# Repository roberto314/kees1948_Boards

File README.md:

# kees1948_Boards
kees 1948 Uniflex Remake

This Repository is for my Remake of the PCBs from kees1948 FLEX and UniFLEX Project.
I like SMD Components and started with a new Version of the CPU09RAM Board with Battery Backup. 

I also started some modifications to the CPUXXCMI Board to run the Exorciser Firmware (Exbug) and in the near future i will make a Exordisk Hardware to read real floppies. See the Exorciser Subdirectory.

This is my Uniflex System:

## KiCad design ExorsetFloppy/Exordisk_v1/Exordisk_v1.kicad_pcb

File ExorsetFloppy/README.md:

# Motorola Exordisk Remake
for kees 1948 Board

This is a Remake of the Motorola Exordisk Board for kees1948 FLEX and UniFLEX Project.
Use it with a CPUXXCMI Board with a 6802 CPU @ 1MHz and the modifications on the Exorciser page.

Exordisk_v1 is the second revision of the Exordisk Board. Use this to build.

Exorset Floppy is the first version of the Exordisk board. It has a lot of problems!

In the GAL subdir. are the equations and .jed files for the exordisk remake board.

This is the Board:

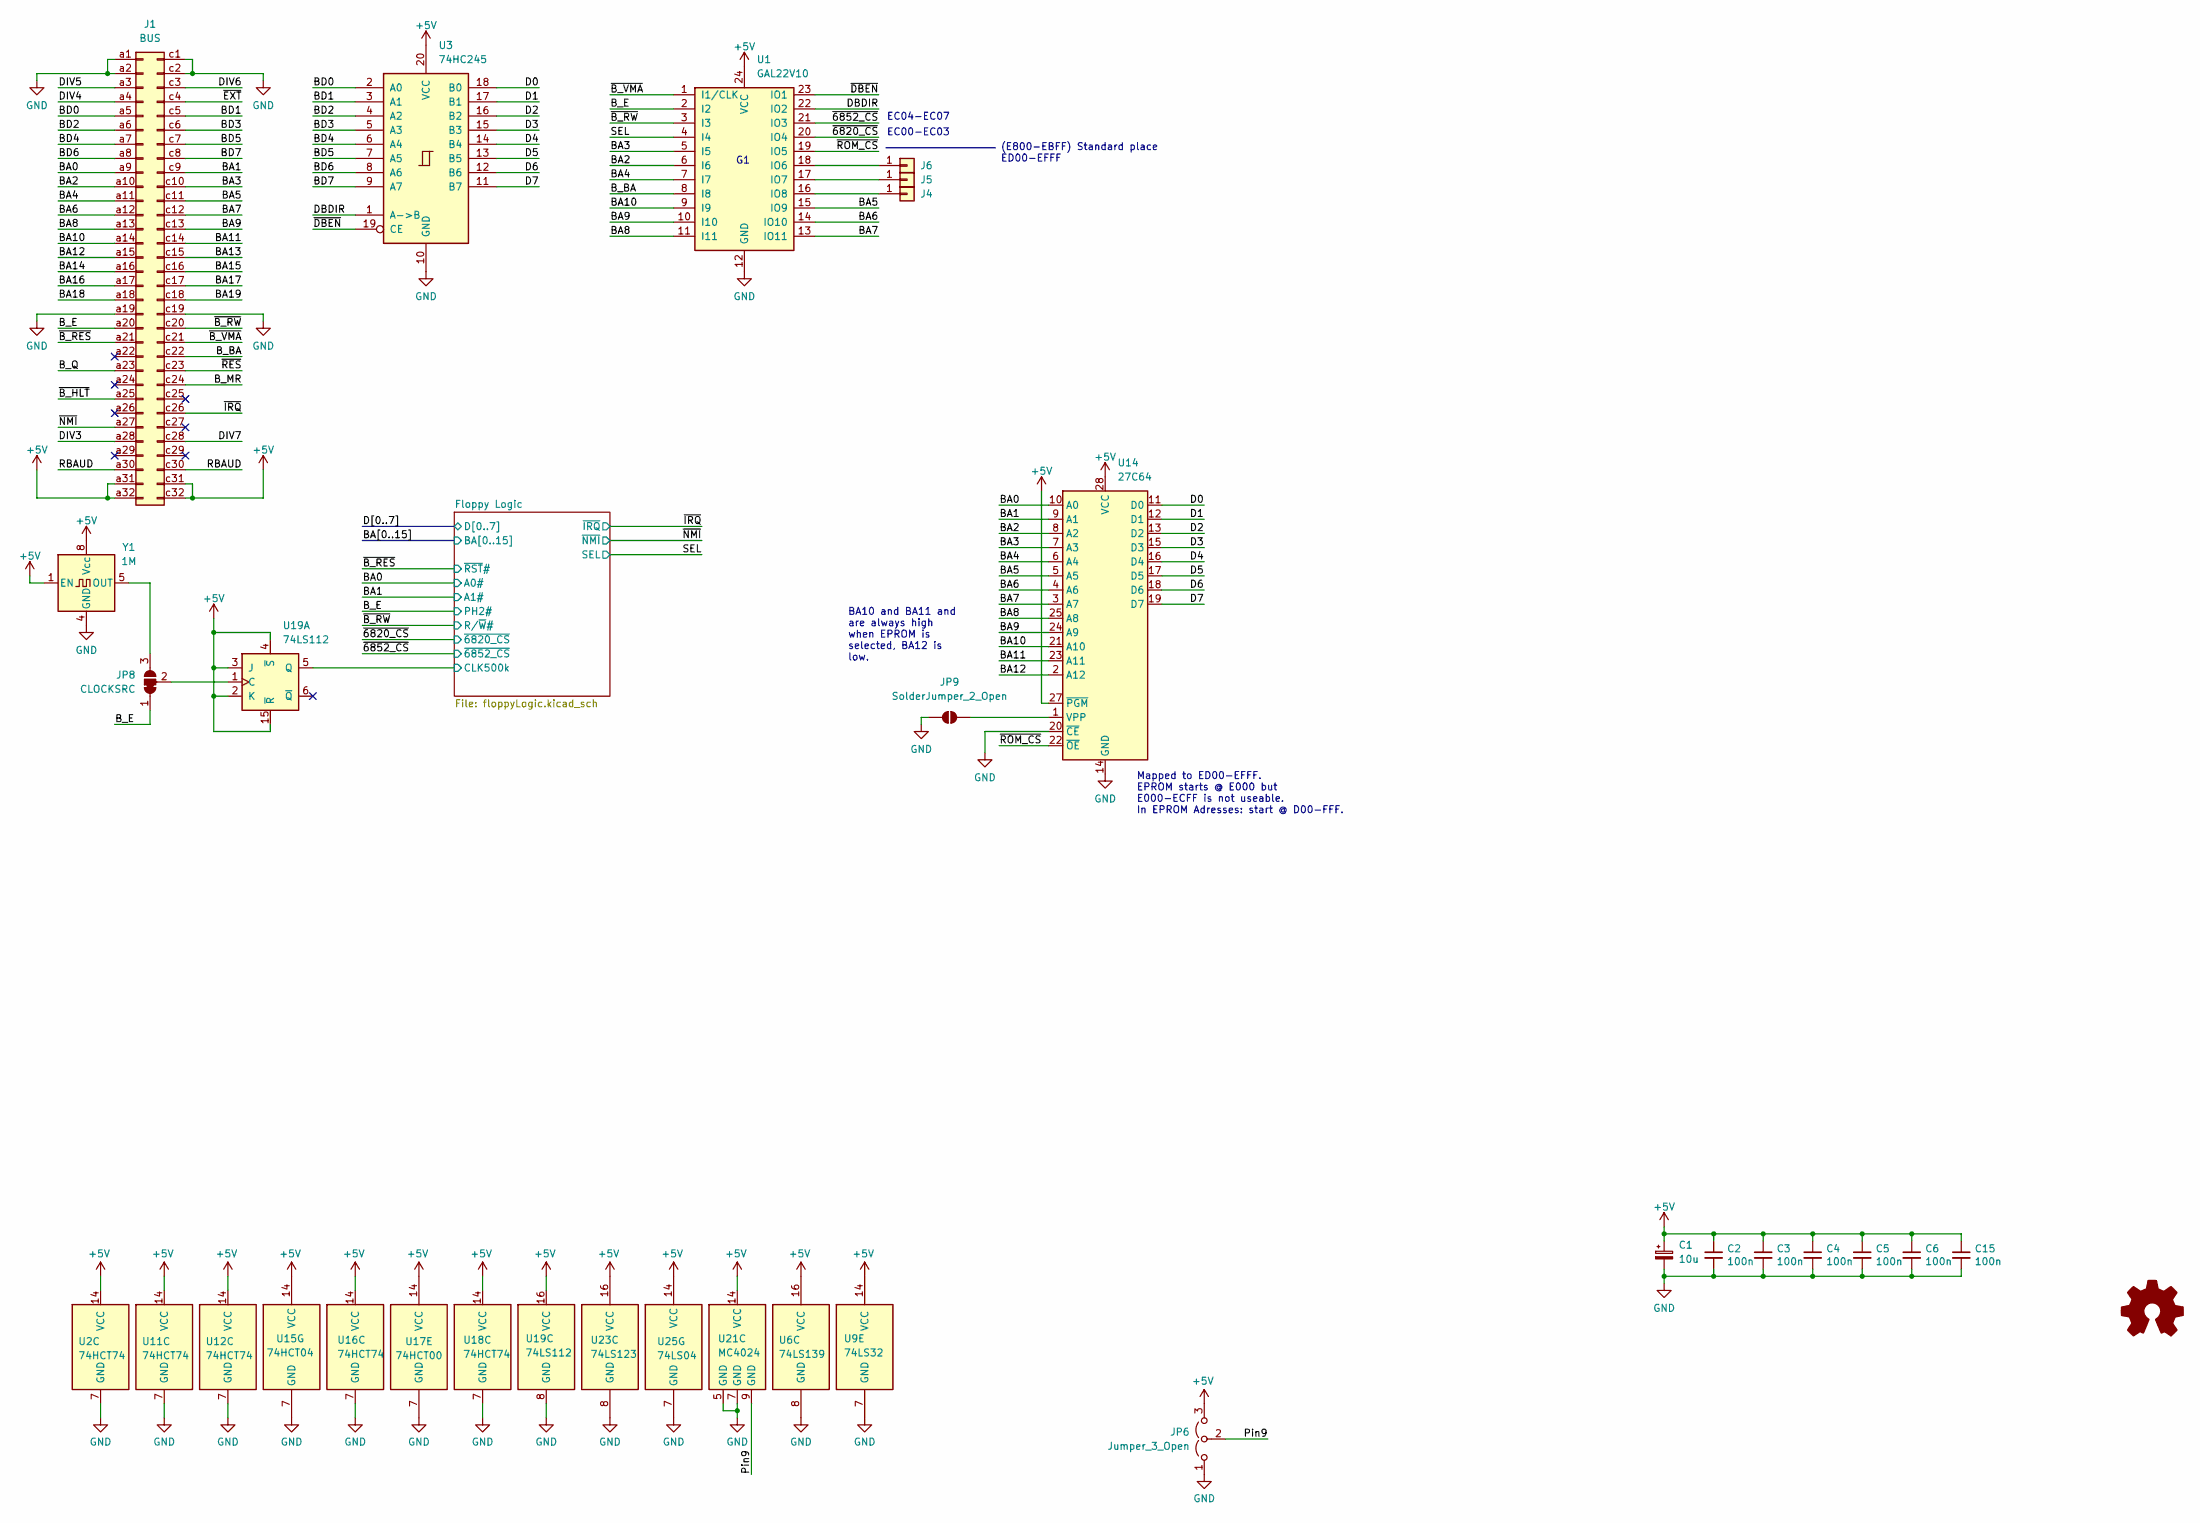
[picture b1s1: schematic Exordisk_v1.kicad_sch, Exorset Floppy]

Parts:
C1: 10u; CP_EIA-7343-31_Kemet-D_HandSolder
C2, C3, C4, C5, C6, C15: 100n; C_1206_3216Metric_Pad1.33x1.80mm_HandSolder
J1: BUS; DIN41612_C_2x32_Male_Horizontal_THT
J4, J5, J6: Conn_01x01; PinHeader_1x01_P2.54mm_Vertical
JP6: Jumper_3_Open; SolderJumper-3_P1.3mm_Open_RoundedPad1.0x1.5mm_NumberLabels
JP8: CLOCKSRC; SolderJumper-3_P1.3mm_Bridged12_RoundedPad1.0x1.5mm_NumberL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
JP9: SolderJumper_2_Open; SolderJumper-2_P1.3mm_Open_Pad1.0x1.5mm
U1: GAL22V10; DIP-24_W7.62mm
U2, U11, U12, U16, U18: 74HCT74; DIP-14_W7.62mm
U3: 74HC245; DIP-20_W7.62mm
U6: 74LS139; DIP-16_W7.62mm
U9: 74LS32; DIP-14_W7.62mm
U14: 27C64; DIP-28_W15.24mm
U15: 74HCT04; DIP-14_W7.62mm
U17: 74HCT00; DIP-14_W7.62mm
U19: 74LS112; DIP-16_W7.62mm
U21: MC4024; DIP-14_W7.62mm
U23: 74LS123; DIP-16_W7.62mm
U25: 74LS04; DIP-14_W7.62mm
Y1: 1M; Oscillator_DIP-8

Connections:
+5V: C1.1, C2.1, C3.1, C4.1, C5.1, C6.1, C15.1, J1.a31, J1.a32, J1.c31, J1.c32, JP6.3 (B), U1.24 (VCC), U2.14 (VCC), U3.20 (VCC), U6.16 (VCC), U9.14 (VCC), U11.14 (VCC), U12.14 (VCC), U14.27 (~PGM), U14.28 (VCC), U15.14 (VCC), U16.14 (VCC), U17.14 (VCC), U18.14 (VCC), U19.2 (K), U19.3 (J), U19.4 (~S), U19.15 (~R), U19.16 (VCC), U21.14 (VCC), U23.16 (VCC), U25.14 (VCC), Y1.1 (EN), Y1.8 (Vcc); also elsewhere on the board
/BA0: J1.a9, U14.10 (A0); also elsewhere on the board
/BA1: J1.c9, U14.9 (A1); also elsewhere on the board
/BA2: J1.a10, U1.6 (I6), U14.8 (A2)
/BA3: J1.c10, U1.5 (I5), U14.7 (A3)
/BA4: J1.a11, U1.7 (I7), U14.6 (A4)
/BA5: J1.c11, U1.15 (IO9), U14.5 (A5)
/BA6: J1.a12, U1.14 (IO10), U14.4 (A6)
/BA7: J1.c12, U1.13 (IO11), U14.3 (A7)
/BA8: J1.a13, U1.11 (I11), U14.25 (A8)
/BA9: J1.c13, U1.10 (I10), U14.24 (A9)
/BA10: J1.a14, U1.9 (I9), U14.21 (A10)
/BA11: J1.c14, U14.23 (A11); also elsewhere on the board
/BA12: J1.a15, U14.2 (A12); also elsewhere on the board
/BA13: J1.c15; also elsewhere on the board
/BA14: J1.a16; also elsewhere on the board
/BA15: J1.c16; also elsewhere on the board
/BA16: J1.a17
/BA17: J1.c17
/BA18: J1.a18
/BA19: J1.c18
/BD0: J1.a5, U3.2 (A0)
/BD1: J1.c5, U3.3 (A1)
/BD2: J1.a6, U3.4 (A2)
/BD3: J1.c6, U3.5 (A3)
/BD4: J1.a7, U3.6 (A4)
/BD5: J1.c7, U3.7 (A5)
/BD6: J1.a8, U3.8 (A6)
/BD7: J1.c8, U3.9 (A7)
/B_BA: J1.c22, U1.8 (I8)
/B_E: J1.a20, JP8.1 (A), U1.2 (I2); also elsewhere on the board
/B_MR: J1.c24
/B_Q: J1.a23
/D0: U3.18 (B0), U14.11 (D0); also elsewhere on the board
/D1: U3.17 (B1), U14.12 (D1); also elsewhere on the board
/D2: U3.16 (B2), U14.13 (D2); also elsewhere on the board
/D3: U3.15 (B3), U14.15 (D3); also elsewhere on the board
/D4: U3.14 (B4), U14.16 (D4); also elsewhere on the board
/D5: U3.13 (B5), U14.17 (D5); also elsewhere on the board
/D6: U3.12 (B6), U14.18 (D6); also elsewhere on the board
/D7: U3.11 (B7), U14.19 (D7); also elsewhere on the board
/DBDIR: U1.22 (IO2), U3.1 (A->B)
/DIV3: J1.a28
/DIV4: J1.a4
/DIV5: J1.a3
/DIV6: J1.c3
/DIV7: J1.c28
/Floppy Logic/CLK500k: U19.5 (Q); also elsewhere on the board
/Pin9: JP6.2 (C), U21.9 (GND)
/RBAUD: J1.a30, J1.c30
/SEL: U1.4 (I4); also elsewhere on the board
/~6820_CS: U1.20 (IO4); also elsewhere on the board
/~6852_CS: U1.21 (IO3); also elsewhere on the board
/~B_HLT: J1.a25
/~B_RES: J1.a21; also elsewhere on the board
/~B_RW: J1.c20, U1.3 (I3); also elsewhere on the board
/~B_VMA: J1.c21, U1.1 (I1/CLK)
/~DBEN: U1.23 (IO1), U3.19 (CE)
/~EXT: J1.c4
/~IRQ: J1.c26; also elsewhere on the board
/~NMI: J1.a27; also elsewhere on the board
/~RES: J1.c23
/~ROM_CS: U1.19 (IO5), U14.22 (~OE)
GND: C1.2, C2.2, C3.2, C4.2, C5.2, C6.2, C15.2, J1.a1, J1.a2, J1.a19, J1.c1, J1.c2, J1.c19, JP6.1 (A), JP9.1 (A), U1.12 (GND), U2.7 (GND), U3.10 (GND), U6.8 (GND), U9.7 (GND), U11.7 (GND), U12.7 (GND), U14.14 (GND), U14.20 (~CE), U15.7 (GND), U16.7 (GND), U17.7 (GND), U18.7 (GND), U19.8 (GND), U21.5 (GND), U21.7 (GND), U23.8 (GND), U25.7 (GND), Y1.4 (GND); also elsewhere on the board
unnamed: J4.1, U1.16 (IO8)
unnamed: J5.1, U1.17 (IO7)
unnamed: J6.1, U1.18 (IO6)
unnamed: JP8.3 (B), Y1.5 (OUT)
unnamed: JP8.2 (C), U19.1 (C)
unnamed: JP9.2 (B), U14.1 (VPP)

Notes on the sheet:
(E800-EBFF) Standard place ED00-EFFF
BA10 and BA11 and are always high when EPROM is selected, BA12 is low.
Mapped to ED00-EFFF. EPROM starts @ E000 but E000-ECFF is not useable. In EPROM Adresses: start @ D00-FFF.
EC00-EC03
EC04-EC07

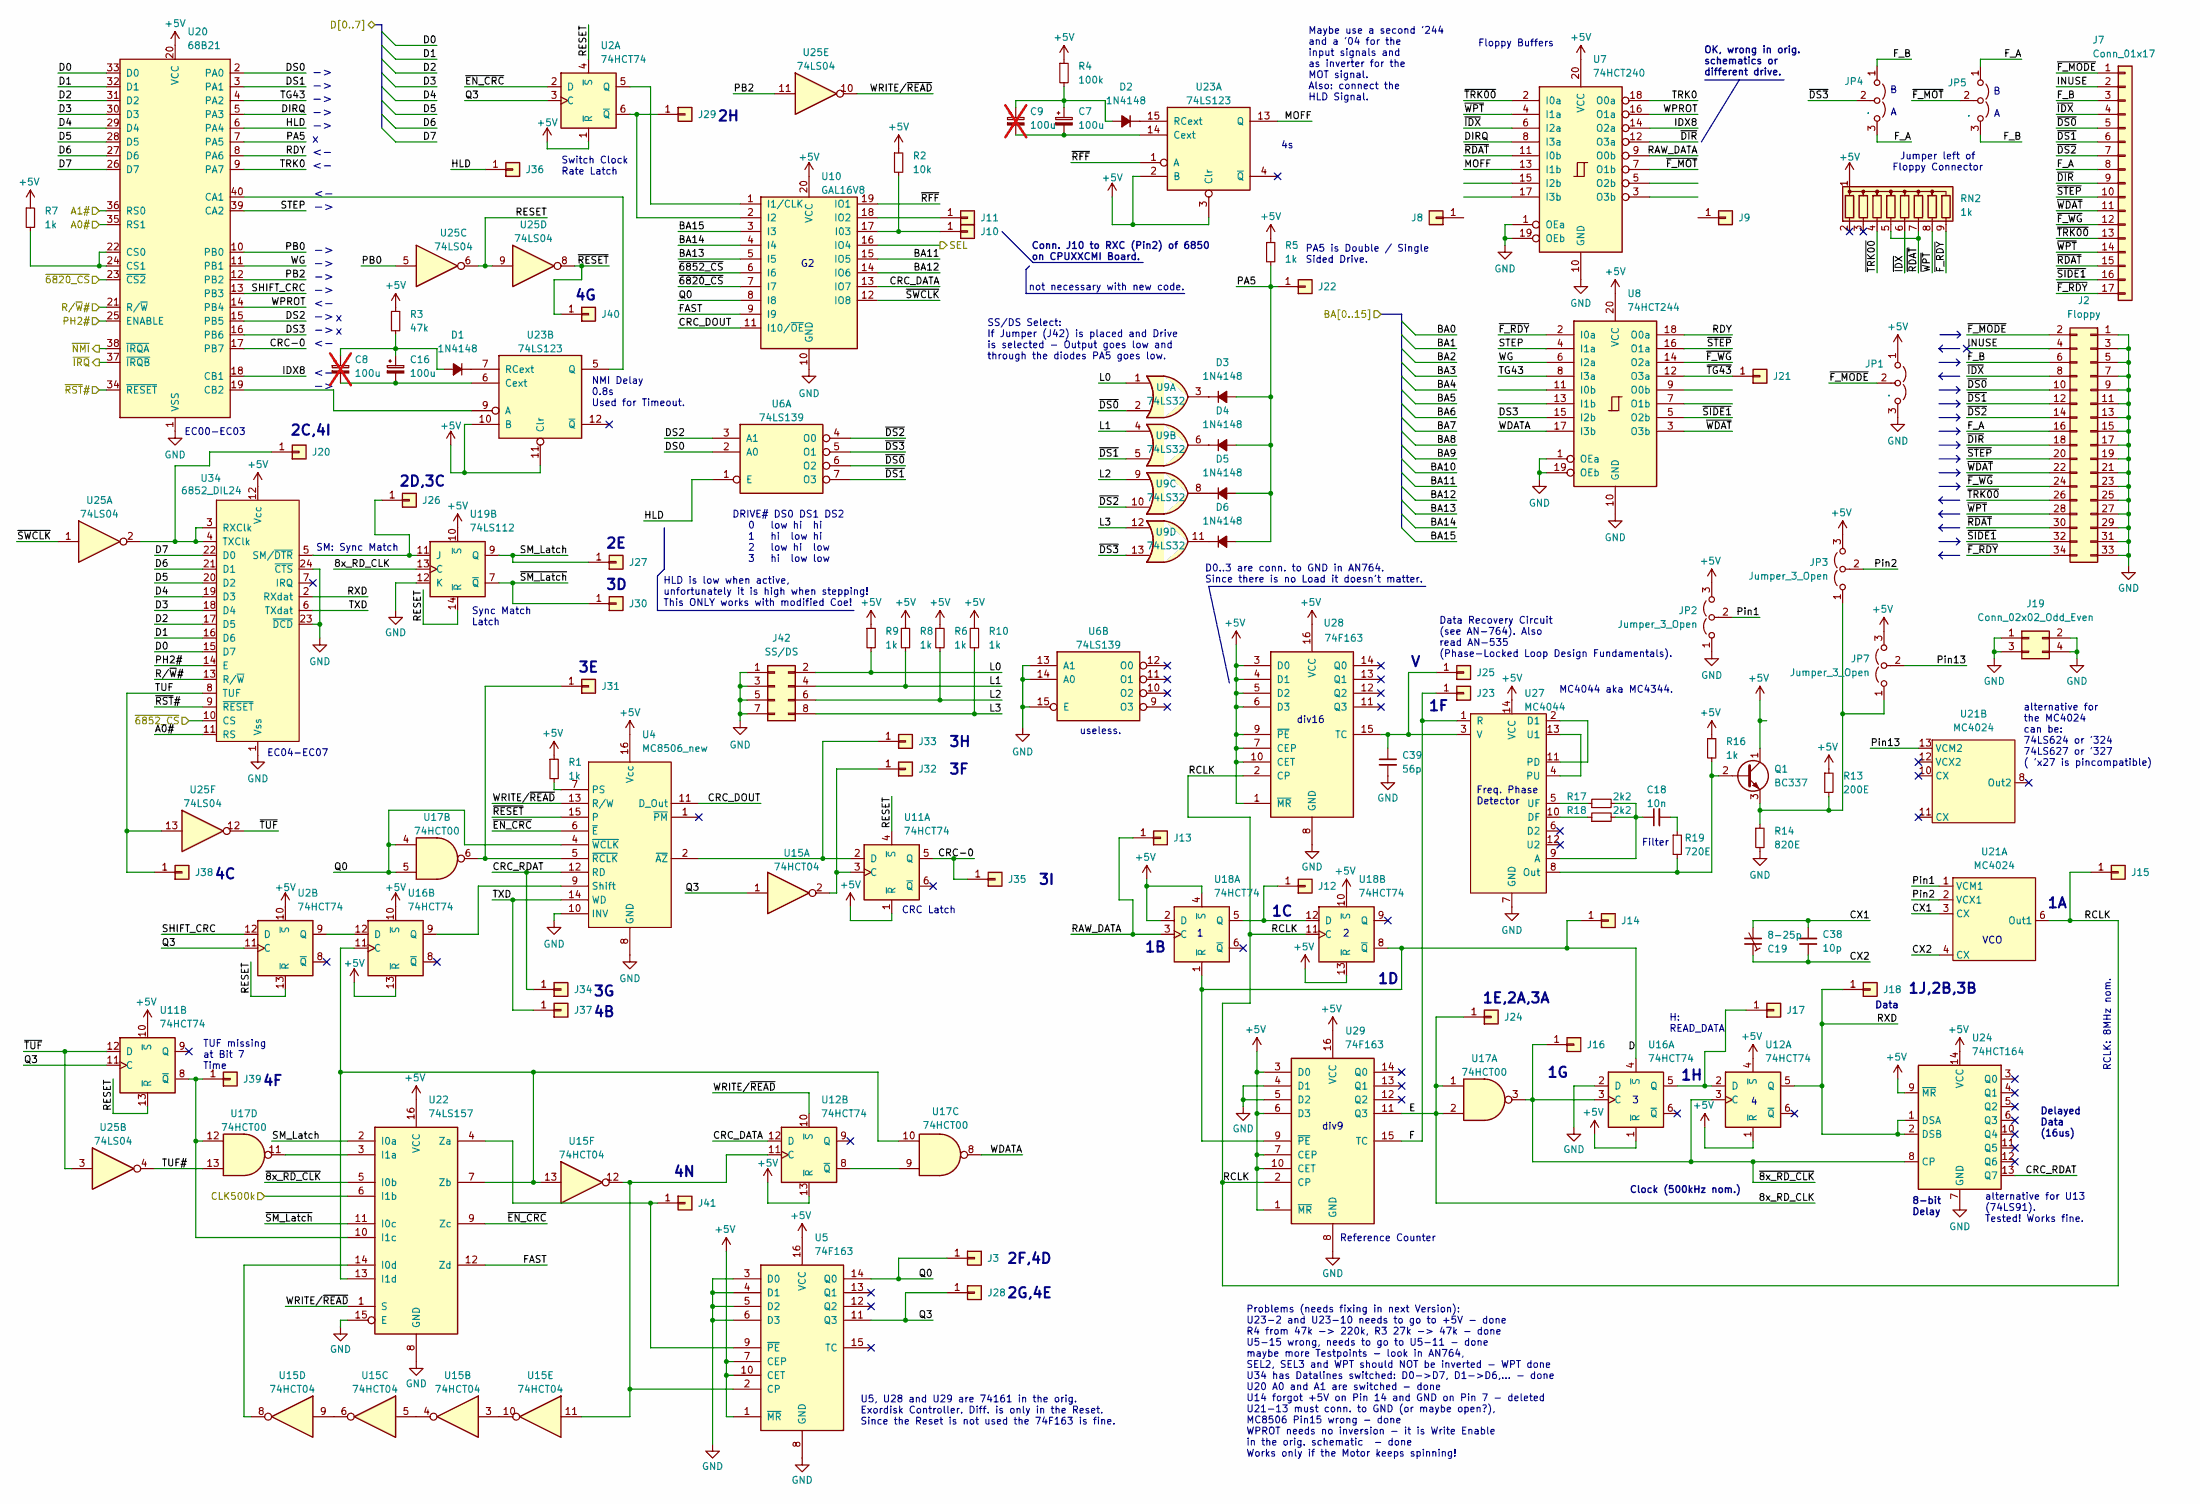
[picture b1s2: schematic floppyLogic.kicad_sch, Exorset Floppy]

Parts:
C7, C16: 100u; CP_EIA-7343-31_Kemet-D_HandSolder
C8, C9: 100u; CP_Radial_D8.0mm_P5.00mm; not fitted
C18: 10n; C_1206_3216Metric_Pad1.33x1.80mm_HandSolder
C19: 8-25p; Capacitor_Trim
C38: 10p; C_1206_3216Metric_Pad1.33x1.80mm_HandSolder
C39: 56p; C_1206_3216Metric_Pad1.33x1.80mm_HandSolder
D1, D2, D3, D4, D5, D6: 1N4148; D_1206_3216Metric_Pad1.42x1.75mm_HandSolder
J2: Floppy; PinHeader_2x17_P2.54mm_Horizontal
J3, J8, J9, J10, J11, J12, J13, J14, J15, J16, J17, J18, J20, J21, J22, J23, J24, J25, J26, J27, J28, J29, J30, J31, J32, J33, J34, J35, J36, J37, J38, J39, J40, J41: Conn_01x01; PinHeader_1x01_P2.54mm_Vertical
J7: Conn_01x17; PinHeader_1x17_P2.54mm_Vertical
J19: Conn_02x02_Odd_Even; PinHeader_2x02_P2.54mm_Vertical
J42: SS/DS; PinHeader_2x04_P2.54mm_Vertical
JP1, JP4, JP5: .; PinHeader_1x03_P2.54mm_Vertical
JP2, JP3, JP7: Jumper_3_Open; SolderJumper-3_P1.3mm_Open_RoundedPad1.0x1.5mm_NumberLabels
Q1: BC337; TO-92L_Wide
R1, R5, R6, R7, R8, R9, R10, R16: 1k; R_1206_3216Metric_Pad1.30x1.75mm_HandSolder
R2: 10k; R_1206_3216Metric_Pad1.30x1.75mm_HandSolder
R3: 47k; R_1206_3216Metric_Pad1.30x1.75mm_HandSolder
R4: 100k; R_1206_3216Metric_Pad1.30x1.75mm_HandSolder
R13: 200E; R_1206_3216Metric_Pad1.30x1.75mm_HandSolder
R14: 820E; R_1206_3216Metric_Pad1.30x1.75mm_HandSolder
R17, R18: 2k2; R_1206_3216Metric_Pad1.30x1.75mm_HandSolder
R19: 720E; R_1206_3216Metric_Pad1.30x1.75mm_HandSolder
RN2: 1k; R_Array_SIP9
U2, U11, U12, U16, U18: 74HCT74; DIP-14_W7.62mm
U4: MC8506_new; DIP-16_W7.62mm
U5, U28, U29: 74F163; DIP-16_W7.62mm
U6: 74LS139; DIP-16_W7.62mm
U7: 74HCT240; DIP-20_W7.62mm
U8: 74HCT244; DIP-20_W7.62mm
U9: 74LS32; DIP-14_W7.62mm
U10: GAL16V8; DIP-20_W7.62mm
U15: 74HCT04; DIP-14_W7.62mm
U17: 74HCT00; DIP-14_W7.62mm
U19: 74LS112; DIP-16_W7.62mm
U20: 68B21; DIP-40_W15.24mm
U21: MC4024; DIP-14_W7.62mm
U22: 74LS157; DIP-16_W7.62mm
U23: 74LS123; DIP-16_W7.62mm
U24: 74HCT164; DIP-14_W7.62mm
U25: 74LS04; DIP-14_W7.62mm
U27: MC4044; DIP-14_W7.62mm
U34: 6852_DIL24; DIP-24_W15.24mm

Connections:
+5V: JP1.1 (A), JP2.3 (B), JP3.3 (B), JP7.3 (B), Q1.1 (C), R1.1, R2.1, R3.1, R4.1, R5.1, R6.1, R7.1, R8.1, R9.1, R10.1, R13.1, R16.1, RN2.1 (common), U2.1 (~R), U2.10 (~S), U4.16 (Vcc), U5.1 (~MR), U5.7 (CEP), U5.10 (CET), U5.16 (VCC), U7.20 (VCC), U8.20 (VCC), U10.20 (VCC), U11.1 (~R), U11.10 (~S), U12.1 (~R), U12.4 (~S), U12.13 (~R), U16.1 (~R), U16.10 (~S), U16.13 (~R), U18.2 (D), U18.4 (~S), U18.10 (~S), U18.13 (~R), U19.10 (~S), U20.20 (VCC), U22.16 (VCC), U23.2 (B), U23.3 (Clr), U23.10 (B), U23.11 (Clr), U24.9 (~MR), U24.14 (VCC), U27.14 (VCC), U28.1 (~MR), U28.3 (D0), U28.4 (D1), U28.5 (D2), U28.6 (D3), U28.7 (CEP), U28.9 (~PE), U28.10 (CET), U28.16 (VCC), U29.1 (~MR), U29.3 (D0), U29.6 (D3), U29.7 (CEP), U29.10 (CET), U29.16 (VCC), U34.12 (Vcc); also elsewhere on the board
/BA0: U20.35 (RS1), U34.11 (RS); also elsewhere on the board
/BA1: U20.36 (RS0); also elsewhere on the board
/BA11: U10.15 (IO5); also elsewhere on the board
/BA12: U10.14 (IO6); also elsewhere on the board
/BA13: U10.5 (I5); also elsewhere on the board
/BA14: U10.4 (I4); also elsewhere on the board
/BA15: U10.3 (I3); also elsewhere on the board
/B_E: U20.25 (ENABLE), U34.14 (E); also elsewhere on the board
/D0: U20.33 (D0), U34.15 (D7); also elsewhere on the board
/D1: U20.32 (D1), U34.16 (D6); also elsewhere on the board
/D2: U20.31 (D2), U34.17 (D5); also elsewhere on the board
/D3: U20.30 (D3), U34.18 (D4); also elsewhere on the board
/D4: U20.29 (D4), U34.19 (D3); also elsewhere on the board
/D5: U20.28 (D5), U34.20 (D2); also elsewhere on the board
/D6: U20.27 (D6), U34.21 (D1); also elsewhere on the board
/D7: U20.26 (D7), U34.22 (D0); also elsewhere on the board
/Floppy Logic/8x_RD_CLK: J24.1, U17.1, U17.2, U19.13 (C), U29.11 (Q3)
/Floppy Logic/CLK500k: U22.6 (I1b); also elsewhere on the board
/Floppy Logic/CRC-0: J35.1, U11.5 (Q), U20.17 (PB7)
/Floppy Logic/CRC_DATA: U10.13 (IO7), U12.12 (D)
/Floppy Logic/CRC_DOUT: U4.11 (D_Out), U10.11 (I10/~OE)
/Floppy Logic/CRC_RDAT: J34.1, U4.12 (RD), U24.13 (Q7)
/Floppy Logic/CX1: C19.2, C38.2, U21.3 (CX)
/Floppy Logic/CX2: C19.1, C38.1, U21.4 (CX)
/Floppy Logic/D: J14.1, U16.4 (~S), U18.1 (~R), U18.8 (~Q), U29.9 (~PE)
/Floppy Logic/DIRQ: U7.8 (I3a), U20.5 (PA3)
/Floppy Logic/DS0: U6.2 (A0), U20.2 (PA0)
/Floppy Logic/DS1: U20.3 (PA1)
/Floppy Logic/DS2: U6.3 (A1), U20.15 (PB5)
/Floppy Logic/DS3: U8.15 (I2b), U20.16 (PB6)
/Floppy Logic/F: J23.1, U27.1 (R), U29.15 (TC)
/Floppy Logic/FAST: U10.9 (I9), U22.12 (Zd)
/Floppy Logic/F_A: J2.16, J7.8, JP4.3 (B), JP5.1 (A)
/Floppy Logic/F_B: J2.6, J7.3, JP4.1 (A), JP5.3 (B)
/Floppy Logic/HLD: J36.1, U6.1 (E), U20.6 (PA4)
/Floppy Logic/IDX8: U7.14 (O2a), U20.18 (CB1)
/Floppy Logic/INUSE: J2.4, J7.2
/Floppy Logic/L0: J42.2, R9.2, U9.1
/Floppy Logic/L1: J42.4, R8.2, U9.4
/Floppy Logic/L2: J42.6, R6.2, U9.9
/Floppy Logic/L3: J42.8, R10.2, U9.12
/Floppy Logic/MOFF: U7.13 (I1b), U23.13 (Q)
/Floppy Logic/PA5: D3.2 (A), D4.2 (A), D5.2 (A), D6.2 (A), J22.1, R5.2, U20.7 (PA5)
/Floppy Logic/PB0: U20.10 (PB0), U25.5
/Floppy Logic/PB2: U20.12 (PB2), U25.11
/Floppy Logic/Pin1: JP2.2 (C), U21.1 (VCM1)
/Floppy Logic/Pin2: JP3.2 (C), U21.2 (VCX1)
/Floppy Logic/Pin13: JP7.2 (C), U21.13 (VCM2)
/Floppy Logic/Q0: J3.1, U4.4 (~WCLK), U5.14 (Q0), U10.8 (I8), U17.4, U17.5
/Floppy Logic/Q3: J28.1, U2.3 (C), U2.11 (C), U5.11 (Q3), U11.11 (C), U15.1
/Floppy Logic/RAW_DATA: J13.1, U7.9 (O0b), U18.3 (C)
/Floppy Logic/RCLK: J15.1, U18.11 (C), U21.6 (Out1), U28.2 (CP), U29.2 (CP)
/Floppy Logic/RDY: U8.18 (O0a), U20.8 (PA6)
/Floppy Logic/RESET: U2.4 (~S), U2.13 (~R), U11.4 (~S), U11.13 (~R), U19.14 (~R), U25.6, U25.9
/Floppy Logic/RXD: J18.1, U12.5 (Q), U24.1 (DSA), U24.2 (DSB), U34.2 (RXdat)
/Floppy Logic/SHIFT_CRC: U2.12 (D), U20.13 (PB3)
/Floppy Logic/SM_Latch: J27.1, U19.9 (Q), U22.2 (I0a)
/Floppy Logic/STEP: U8.4 (I1a), U20.39 (CA2)
/Floppy Logic/TG43: U8.8 (I3a), U20.4 (PA2)
/Floppy Logic/TRK0: U7.18 (O0a), U20.9 (PA7)
/Floppy Logic/TUF: J38.1, U25.13, U34.8 (TUF)
/Floppy Logic/TUF#: U17.13, U25.4
/Floppy Logic/TXD: J37.1, U4.14 (WD), U34.6 (TXdat)
/Floppy Logic/WDATA: U8.17 (I3b), U17.8
/Floppy Logic/WG: U8.6 (I2a), U20.11 (PB1)
/Floppy Logic/WPROT: U7.16 (O1a), U20.14 (PB4)
/Floppy Logic/WRITE/~READ: U4.13 (R/W), U12.10 (~S), U22.1 (S), U25.10
/Floppy Logic/~8x_RD_CLK: J16.1, U12.3 (C), U16.3 (C), U17.3, U22.5 (I0b), U24.8 (CP)
/Floppy Logic/~DIR: J2.18, J7.9, U7.12 (O3a)
/Floppy Logic/~DS0: J2.10, J7.5, U6.6 (O2), U9.2
/Floppy Logic/~DS1: J2.12, J7.6, U6.7 (O3), U9.5
/Floppy Logic/~DS2: J2.14, J7.7, U6.4 (O0), U9.10
/Floppy Logic/~DS3: JP4.2 (C), U6.5 (O1), U9.13
/Floppy Logic/~EN_CRC: U2.2 (D), U4.6 (~E), U22.9 (Zc)
/Floppy Logic/~F_MODE: J2.2, J7.1, JP1.2 (C)
/Floppy Logic/~F_MOT: JP5.2 (C), U7.7 (O1b)
/Floppy Logic/~F_RDY: J2.34, J7.17, RN2.9 (R8), U8.2 (I0a)
/Floppy Logic/~F_WG: J2.24, J7.12, U8.14 (O2a)
/Floppy Logic/~IDX: J2.8, J7.4, RN2.6 (R5), U7.6 (I2a)
/Floppy Logic/~RDAT: J2.30, J7.15, RN2.5 (R4), RN2.7 (R6), U7.11 (I0b)
/Floppy Logic/~RESET: J40.1, U4.15, U25.8
/Floppy Logic/~RFF: U10.19 (IO1), U23.1 (A)
/Floppy Logic/~SIDE1: J2.32, J7.16, U8.5 (O2b)
/Floppy Logic/~SM_Latch: J30.1, U19.7 (~Q), U22.11 (I0c)
/Floppy Logic/~STEP: J2.20, J7.10, U8.16 (O1a)
/Floppy Logic/~SWCLK: U10.12 (IO8), U25.1
/Floppy Logic/~TG43: J21.1, U8.12 (O3a)
/Floppy Logic/~TRK00: J2.26, J7.13, RN2.4 (R3), U7.2 (I0a)
/Floppy Logic/~TUF: U11.12 (D), U25.3, U25.12
/Floppy Logic/~WDAT: J2.22, J7.11, U8.3 (O3b)
/Floppy Logic/~WPT: J2.28, J7.14, RN2.8 (R7), U7.4 (I1a)
/SEL: U10.16 (IO4); also elsewhere on the board
/~6820_CS: U10.7 (I7), U20.23 (~CS2); also elsewhere on the board
/~6852_CS: U10.6 (I6), U34.10 (CS); also elsewhere on the board
/~B_RES: U20.34 (~RESET), U34.9 (~RESET); also elsewhere on the board
/~B_RW: U20.21 (R/~W), U34.13 (R/~W); also elsewhere on the board
/~IRQ: U20.37 (~IRQB); also elsewhere on the board
/~NMI: U20.38 (~IRQA); also elsewhere on the board
GND: C39.2, J2.1, J2.3, J2.5, J2.7, J2.9, J2.11, J2.13, J2.15, J2.17, J2.19, J2.21, J2.23, J2.25, J2.27, J2.29, J2.31, J2.33, J19.1, J19.2, J19.3, J19.4, J42.1, J42.3, J42.5, J42.7, JP1.3 (B), JP2.1 (A), R14.2, U4.8 (GND), U4.10 (INV), U5.3 (D0), U5.4 (D1), U5.5 (D2), U5.6 (D3), U5.8 (GND), U6.13 (A1), U6.14 (A0), U6.15 (E), U7.1 (OEa), U7.10 (GND), U7.19 (OEb), U8.1 (OEa), U8.10 (GND), U8.19 (OEb), U10.10 (GND), U16.2 (D), U19.12 (K), U20.1 (VSS), U22.8 (GND), U22.15 (E), U24.7 (GND), U27.7 (GND), U28.8 (GND), U29.4 (D1), U29.5 (D2), U29.8 (GND), U34.1 (Vss), U34.23 (~DCD), U34.24 (~CTS); also elsewhere on the board
unnamed: C18.2, R19.1
unnamed: C8.1, C16.1, D1.2 (A), R3.2
unnamed: D1.1 (K), U23.7 (RCext)
unnamed: C7.1, C9.1, D2.2 (A), R4.2
unnamed: D2.1 (K), U23.15 (RCext)
unnamed: D3.1 (K), U9.3
unnamed: D4.1 (K), U9.6
unnamed: D5.1 (K), U9.8
unnamed: D6.1 (K), U9.11
unnamed: J10.1, R2.2, U10.17 (I03)
unnamed: J11.1, U10.18 (IO2)
unnamed: J12.1, U18.5 (Q), U18.12 (D)
unnamed: J17.1, U12.2 (D), U16.5 (Q)
unnamed: J20.1, U25.2, U34.3 (RXClk), U34.4 (TXClk)
unnamed: C39.1, J25.1, U27.3 (V), U28.15 (TC)
unnamed: J26.1, U19.11 (J), U34.5 (SM/~DTR)
unnamed: J29.1, U2.6 (~Q), U10.2 (I2)
unnamed: J31.1, U4.5 (~RCLK), U17.6
unnamed: J32.1, U11.3 (C), U15.2
unnamed: J33.1, U4.2 (~AZ), U11.2 (D)
unnamed: J39.1, U11.8 (~Q), U17.12, U22.10 (I1c)
unnamed: J41.1, U5.9 (~PE), U22.4 (Za)
unnamed: JP3.1 (A), JP7.1 (A), Q1.3 (E), R13.2, R14.1
unnamed: Q1.2 (B), R16.2, R19.2, U27.8 (Out)
unnamed: R1.2, U4.7 (PS)
unnamed: U2.5 (Q), U10.1 (I1/CLK)
unnamed: U5.2 (CP), U12.11 (C), U15.11, U15.12
unnamed: U12.8 (~Q), U17.9
unnamed: U15.4, U15.5
unnamed: U15.6, U15.9
unnamed: U15.3, U15.10
unnamed: U15.13, U16.11 (C), U17.10, U22.7 (Zb), U22.13 (I1d)
unnamed: U2.9 (Q), U16.12 (D)
unnamed: U4.9 (Shift), U16.9 (Q)
unnamed: U20.40 (CA1), U23.5 (Q)
unnamed: U20.19 (CB2), U23.9 (A)
unnamed: R7.2, U20.22 (CS0), U20.24 (CS1)
unnamed: U15.8, U22.14 (I0d)
unnamed: U17.11, U22.3 (I1a)
unnamed: C7.2, C9.2, U23.14 (Cext)
unnamed: C8.2, C16.2, U23.6 (Cext)
unnamed: C18.1, R17.2, R18.2, U27.9 (A)
unnamed: U27.2 (D1), U27.11 (PD)
unnamed: R18.1, U27.10 (DF)
unnamed: U27.4 (PU), U27.13 (U1)
unnamed: R17.1, U27.5 (UF)

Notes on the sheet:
<- ->
alternative for the MC4024 can be: 74LS624 or '324 74LS627 or '327 ( 'x27 is pincompatible)
SS/DS Select: If Jumper (J42) is placed and Drive is selected - Output goes low and through the diodes PA5 goes low.
NMI Delay 0.8s Used for Timeout.
MC4044 aka MC4344.
Problems (needs fixing in next Version): U23-2 and U23-10 needs to go to +5V - done R4 from 47k -> 220k, R3 27k -> 47k - done U5-15 wrong, needs to go to U5-11 - done maybe more Testpoints - look in AN764, SEL2, SEL3 and WPT should NOT be inverted - WPT done U34 has Datalines switched: D0->D7, D1->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
DRIVE# DS0 DS1 DS2 0 low hi hi 1 hi low hi 2 low hi low 3 hi low low
HLD is low when active, unfortunately it is high when stepping! This ONLY works with modified Coe!
Freq. Phase Detector
CRC Latch
D0..3 are conn. to GND in AN764. Since there is no Load it doesn't matter.
Data Recovery Circuit (see AN-764). Also read AN-535 (Phase-Locked Loop Design Fundamentals).
x x
EC00-EC03
2C,4I
useless.
div9
TUF missing at Bit 7 Time
RCLK: 8MHz nom.
Sync Match Latch
not necessary with new code.
Data
1E,2A,3A
1J,2B,3B
Clock (500kHz nom.)
B A
-> -> -> -> <- -> -> <-
SM: Sync Match
OK, wrong in orig. schematics or different drive.
PA5 is Double / Single Sided Drive.
2F,4D
Conn. J10 to RXC (Pin2) of 6850 on CPUXXCMI Board.
Floppy Buffers
Switch Clock Rate Latch
Filter
H: READ_DATA
Maybe use a second '244 and a '04 for the input signals and as inverter for the MOT signal. Also: connect the HLD Signal.
Jumper left of Floppy Connector
2D,3C
U5, U28 and U29 are 74161 in the orig. Exordisk Controller. Diff. is only in the Reset. Since the Reset is not used the 74F163 is fine.

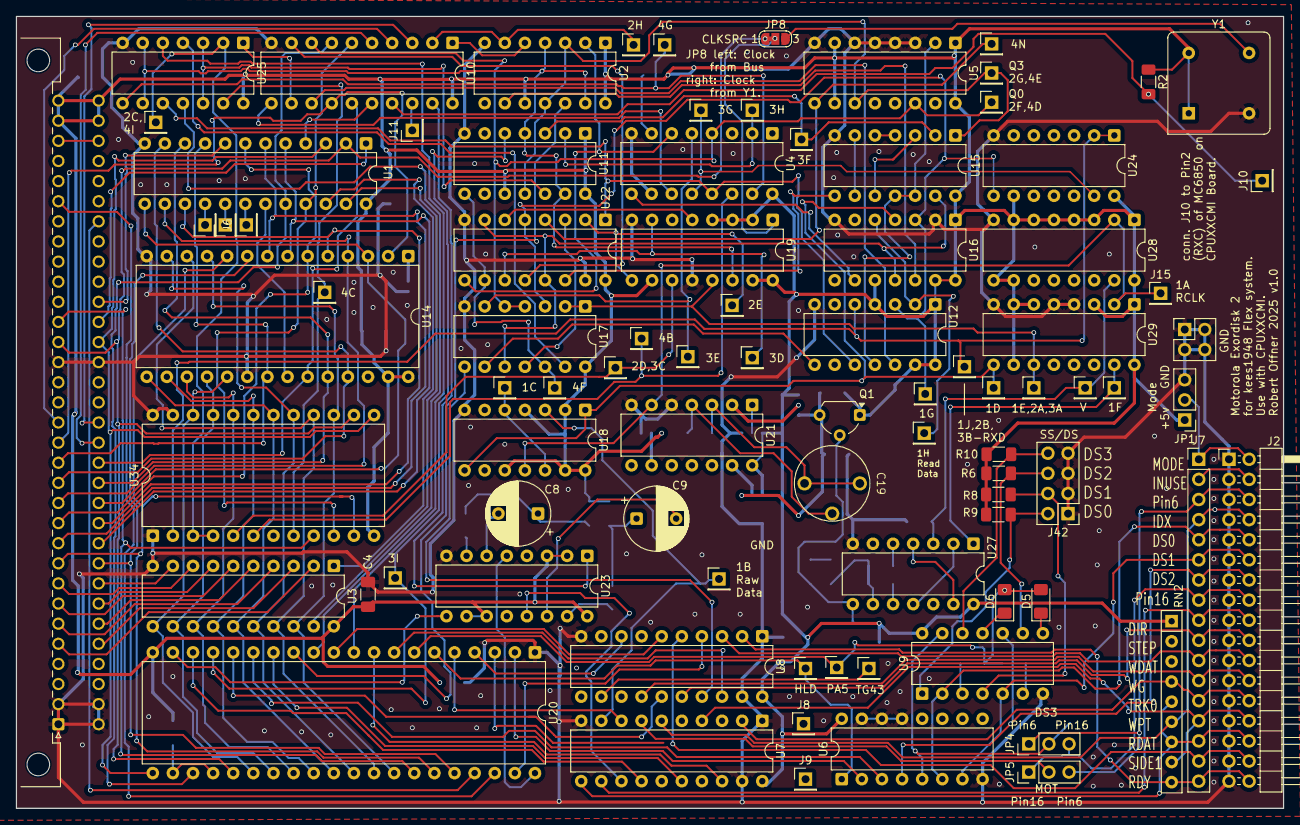
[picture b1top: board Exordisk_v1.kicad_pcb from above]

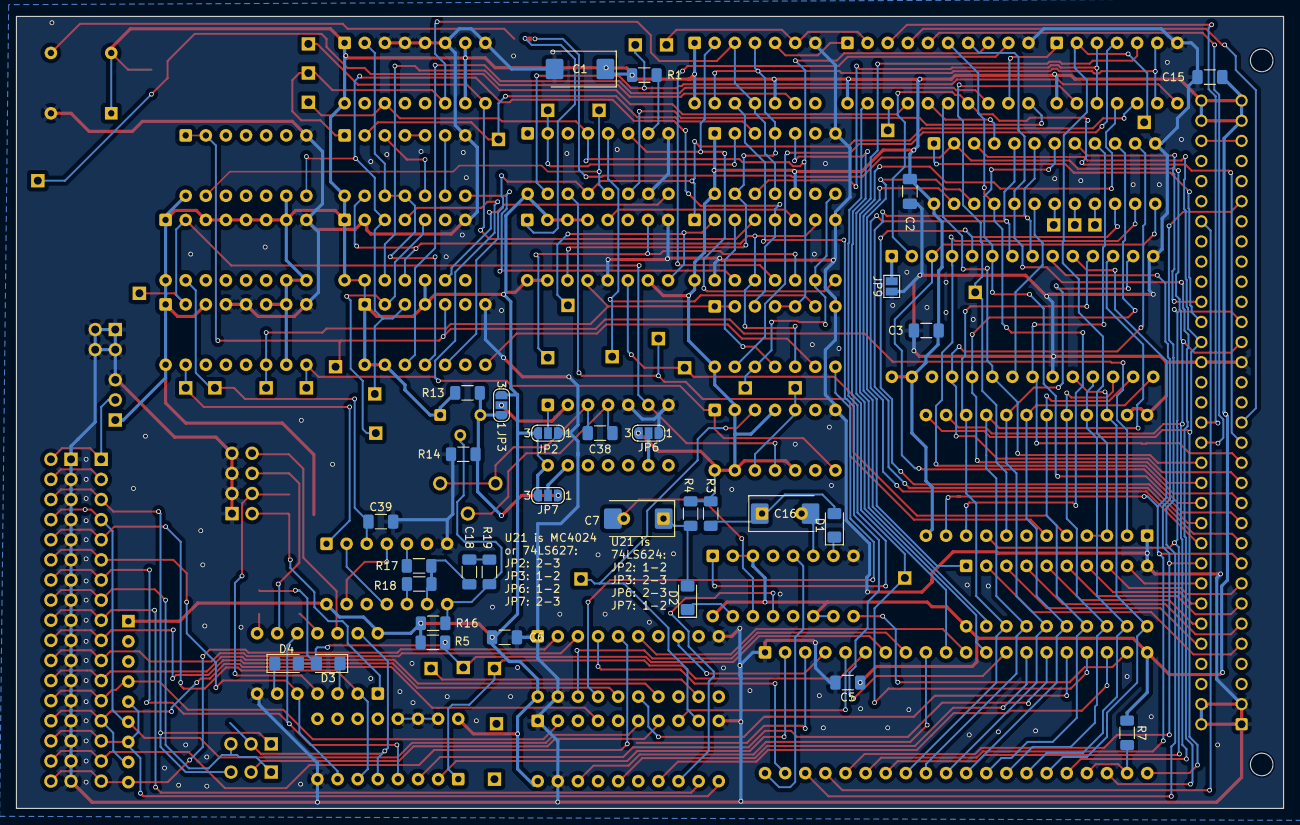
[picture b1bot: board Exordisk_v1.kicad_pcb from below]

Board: 2 copper layers, 160.0 x 100.0 mm, 119 parts (31 on the bottom side), 175 nets.
